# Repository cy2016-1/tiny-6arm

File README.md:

### 一、机械臂简介

机械制作方面采用铝型材、3D打印、同步带和步进电机，低成本的制作方案。控制器方面，使用esp32s3芯片，带有WiFi蓝牙功能。可以输出100KHZ脉冲，支持关节运动和直线运动指令，150mA 8路输出，6~36V 8路输入，带光耦隔离。编程方面，采用blockly可视化编程，使用手机或平板就可以完成编程。

### 二、制作过程

#### 1.机械部分

首先使用FreeCAD软件进行3D模型图绘制。FreeCAD是一个开源的3D设计软件，可以免费使用，方便二次开发，支持运动仿真和简单的有限元仿真。我使用它来设计我的机械臂。其中前三关节采用双电机结构，也就是说一个关节有两个电机，这样平衡的设计既提高了负载能力，也提高了精度和稳定性。现在这台机械臂拥有3kg负载能力和0.5mm的重複定位精度，以及765mm的臂长。

#### 2.控制器部分

##### 2.1 主控制器

主控制器采用ESP32-S3芯片，ESP32-S3芯片带有WiFi蓝牙功能，双核，240Mhz频率，45 个可编程 GPIO。性能可以满足机械臂运行算法，设计了6个脉冲控制接口，可以控制6轴机械臂。8路输入和8路输出，带光电耦合起到保护电路的作用，方便外接电磁阀。

##### 2.2 电机驱动部分

步进电机驱动采用TB67S109AFTG芯片，支持最大4A电流。控制芯片使用ESP32-C3，支持脉冲控制和CAN通信控制。磁编码器使用MT6816CT-ACD，14位单圈绝度编码器，最高精度可达0.02°。

##### 2.3 软件部分

主控板程序是基于开源micropython的，它实现了使用python语言就可完成单片机程序开发。驱动板编程是基于ESP-IDF库编写的C语言程序。手机控制软件是基于开源blockly和bipes编写的。

软件下载时使用USB转串口下载，电机驱动板下载前按住按键然后上电进入下载模式，下载完成后需要校准编码器。校准方法是：电机无负载上电 >> 蓝色LED亮时按住按键 >> 进入自动校准模式。

| 电路板        | 程序        | 固件 |
|-----------|--------------|-------|
| 控制器 | robot.c   | robot.bin   |
| 1-1轴 | step1-1.c  | step1-1.bin |
| 1-2轴 | step1-2.c  | step1-2.bin |
| 2-1轴 | step2-1.c  | step2-1.bin |
| 2-2轴 | step2-1.c  | step2-2.bin |
| 3-1轴 | step3-1.c  | step3-1.bin |
| 3-2轴 | step3-2.c  | step3-2.bin |
| 4-1轴 | step4-1.c  | step4-1.bin |
| 5-1轴 | step5-1.c  | step5-1.bin |
| 6-1轴 | step6-1.c  | step6-1.bin |

### 三、使用说明

注意：用手拖动到初始位置再通电，此时作为坐标原点。

#### 3.1 手机或平板编程

#### 3.2 电脑编程（Thonny软件）

#### 3.3 RS485通信

控制板带有RS485通信接口，可以使用modbus协议控制和读取机械臂的状态

默认参数：波特率：9600，数据位：8，校验：无，停止位：1，modbus站口：1

| 地址        | 读/写       | 说明       |
|-----------|--------------|-------|
| 0~99   |     读/写        |   系统变量，支持断电保存 |
| 100~149   |     读/写        |   未使用  |
| 150   |     读/写        |   机械臂全局速度 |
| 151   |     读        |   机械臂实时速度    |
| 152   |     读/写        |   机械臂目标速度    |
| 153   |     读        |   机械臂实时加速度    |
| 152   |     读/写        |   机械臂目标加速度    |
| 160~165   |     读        |   机械臂6个关节实时脉冲数  |
| 170~175   |     读/写        |   机械臂6个关节目标脉冲数  |
| 180~185   |     读        |   机械臂6个关节实时力矩  |
| 190   |     读/写        |   设置modbus波特率： 0:9600, 1:19200, 2:38400, 3:57600, 4:112500 |
| 191   |     读/写        |   设置modbus数据位： 0:8位,  1:7位 |
| 192   |     读/写        |   设置modbus校验： 0:无校验, 1:奇校验, 2:偶校验|
| 193   |     读/写        |   设置modbus停止位： 0:1位,  1:2位 |
| 194   |     读/写        |   设置modbus站口，默认是1，  范围：1~256 |

### 四、项目收入

| 时间        | 收入类型         | 金额（元） |
|-----------|--------------|-------|
| 2021-2022   |     嘉立创-星火计划金奖        |   10000|
| 2021-2022   |     用户咨询赞助         |   500    |
| 2021-2022 | 哔哩哔哩视频       |  100   |
| 2020-2021 | 贸泽电子-短视频大赛金奖 | 2000  |
| 2020-2021 | 用户咨询赞助       | 200   |
| 2020-2021 | 哔哩哔哩视频       | 200   |

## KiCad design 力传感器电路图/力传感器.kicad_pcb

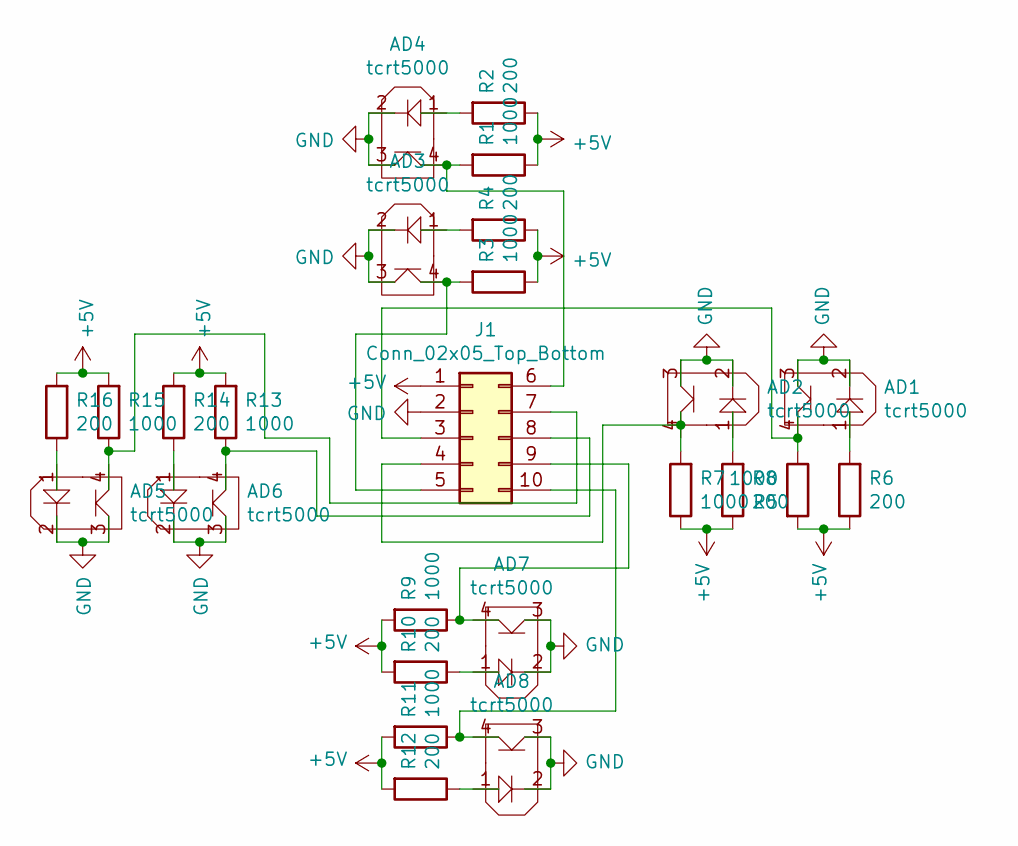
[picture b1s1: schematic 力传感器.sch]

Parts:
AD1, AD2, AD3, AD4, AD5, AD6, AD7, AD8: tcrt5000
J1: Conn_02x05_Top_Bottom; PinHeader_2x05_P2.54mm_Vertical
R1, R3, R5, R7, R9, R11, R13, R15: 1000; R_Axial_DIN0207_L6.3mm_D2.5mm_P10.16mm_Horizontal
R2, R4, R6, R8, R10, R12, R14, R16: 200; R_Axial_DIN0207_L6.3mm_D2.5mm_P10.16mm_Horizontal

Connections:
+5V: J1.1, R1.1, R2.1, R3.1, R4.1, R5.2, R6.1, R7.1, R8.1, R9.2, R10.2, R11.2, R12.2, R13.2, R14.2, R15.2, R16.2
GND: AD1.2, AD1.3, AD2.2, AD2.3, AD3.2, AD3.3, AD4.2, AD4.3, AD5.2, AD5.3, AD6.2, AD6.3, AD7.2, AD7.3, AD8.2, AD8.3, J1.2
unnamed: AD1.1, R6.2
unnamed: AD1.4, J1.3, R5.1
unnamed: AD2.1, R8.2
unnamed: AD2.4, J1.4, R7.2
unnamed: AD3.1, R4.2
unnamed: AD3.4, J1.5, R3.2
unnamed: AD4.1, R2.2
unnamed: AD4.4, J1.6, R1.2
unnamed: AD5.1, R16.1
unnamed: AD5.4, J1.7, R15.1
unnamed: AD6.1, R14.1
unnamed: AD6.4, J1.8, R13.1
unnamed: AD7.1, R10.1
unnamed: AD7.4, J1.9, R9.1
unnamed: AD8.1, R12.1
unnamed: AD8.4, J1.10, R11.1

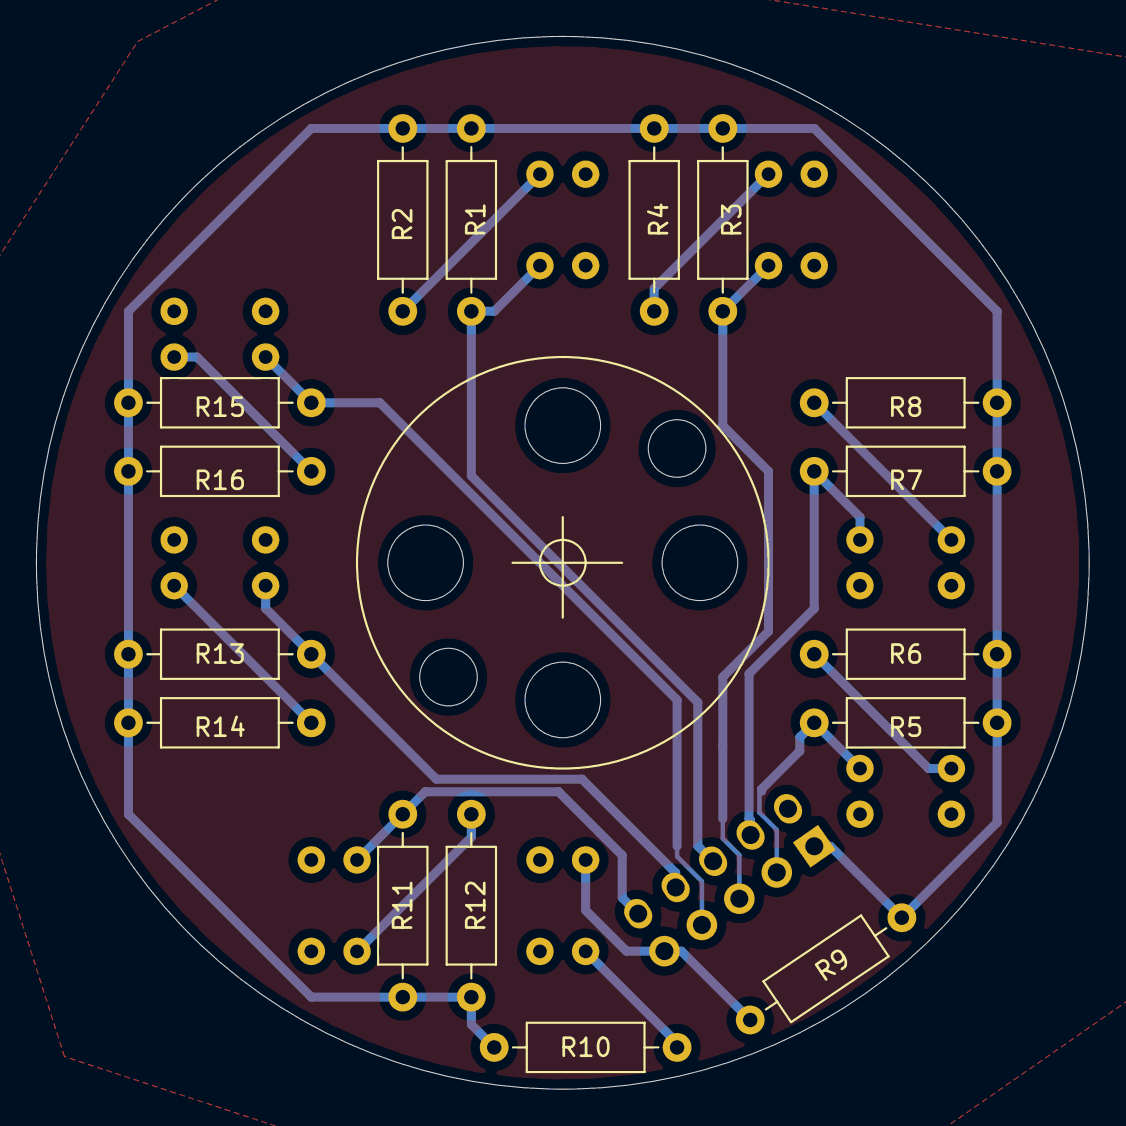
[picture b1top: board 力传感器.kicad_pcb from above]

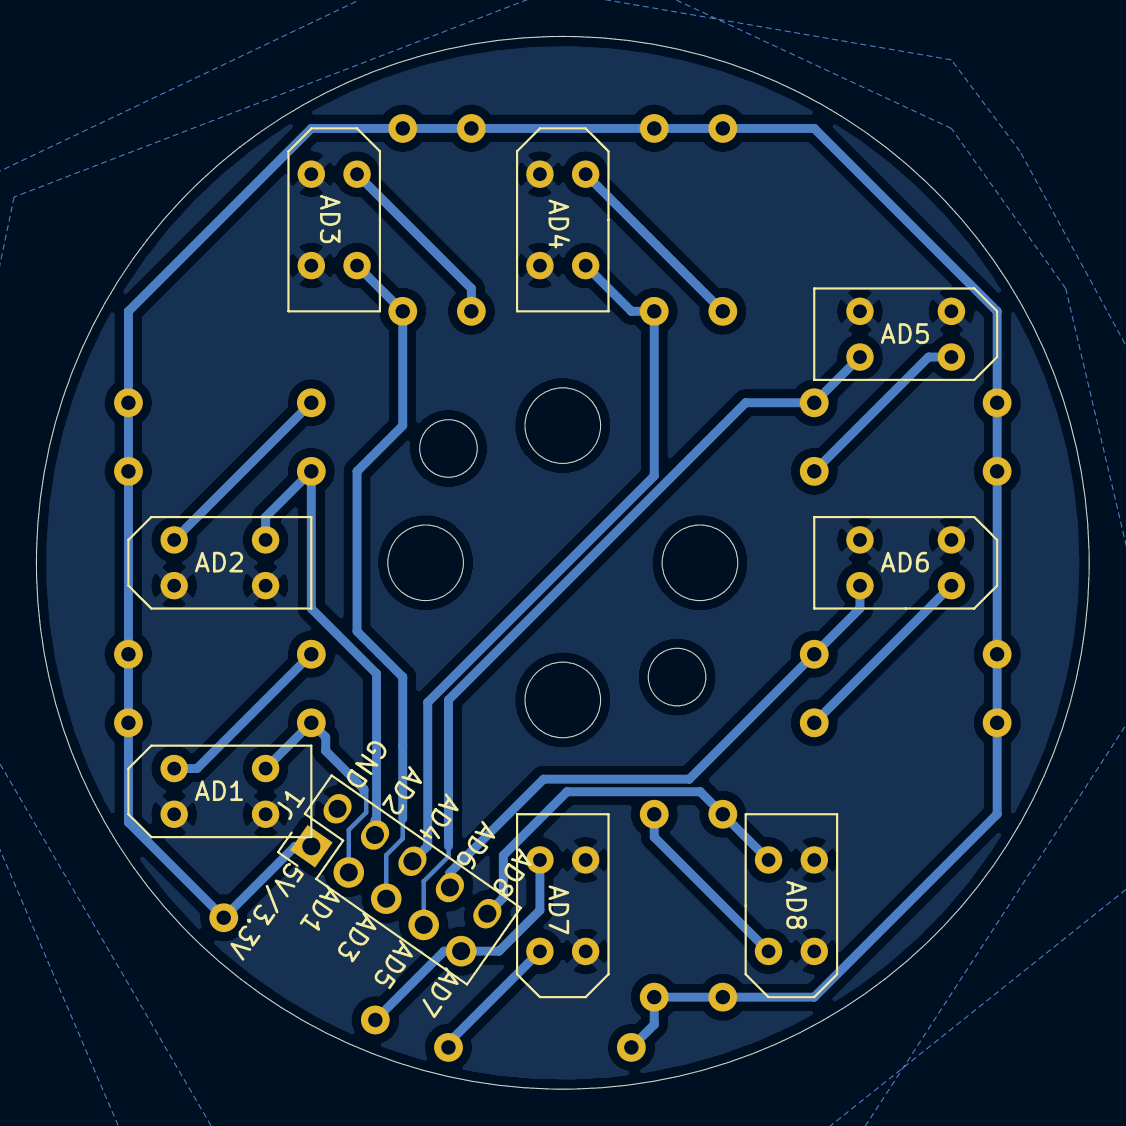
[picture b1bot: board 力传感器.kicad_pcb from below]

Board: 2 copper layers, 58.5 x 58.5 mm, 25 parts (9 on the bottom side), 18 nets.

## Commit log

2021-10-21 add LICENSE.
2021-10-21 新建 3D模型图
2021-10-21 新建 程序文件
2021-10-21 重命名 3D模型图/力传感器4.FCStd 为 3D模型图/力传感器.FCStd
2021-10-21 update README.md.
2021-10-21 更新程序
2021-10-27 test
2022-05-27 新建 MC3
2022-05-27 重命名 MC3 为 MC3监控系统
2022-07-16 新建 图片
2022-08-18 add 图片/1.txt.
2022-08-18 add 图片/1.md.
2022-08-18 update 图片/1.md.
2022-08-18 update 图片/1.txt.
2022-09-19 删除文件 MC3监控系统
2022-09-19 删除文件 程序文件
2022-09-19 add 控制器程序.
2022-09-19 删除文件 控制器程序
2022-09-19 新建 控制器程序
2022-09-19 删除文件 图片/1.md
2022-09-19 删除文件 图片/1.txt
2022-09-19 删除文件 图片.png
2022-09-19 删除文件 机械臂开发购买零件.docx
2022-09-19 删除文件 力传感器电路图
2022-09-19 新建 由于文件太大无法上传请带立创开源下载
2022-09-19 删除文件 3D模型图/6轴机械臂.FCStd
2022-09-19 删除文件 3D模型图/力传感器.FCStd
2022-09-19 删除文件 3D模型图/机械臂blender仿真.blend
2022-09-19 add 3D模型图/由于文件太大无法上传请带立创开源下载.
2022-09-19 删除文件 3D模型图/由于文件太大无法上传请带立创开源下载
2022-09-19 update 3D模型图/由于文件太大无法上传请带立创开源下载.
2023-01-06 重命名 控制器程序 为 程序
2023-01-06 删除文件 程序/robot.zip
2023-01-06 删除文件 程序/firmware37.bin
2023-01-06 删除文件 程序/robot.c
2023-01-06 删除文件 程序/step1-1.c
2023-01-06 重命名 3D模型图 为 3D模型
